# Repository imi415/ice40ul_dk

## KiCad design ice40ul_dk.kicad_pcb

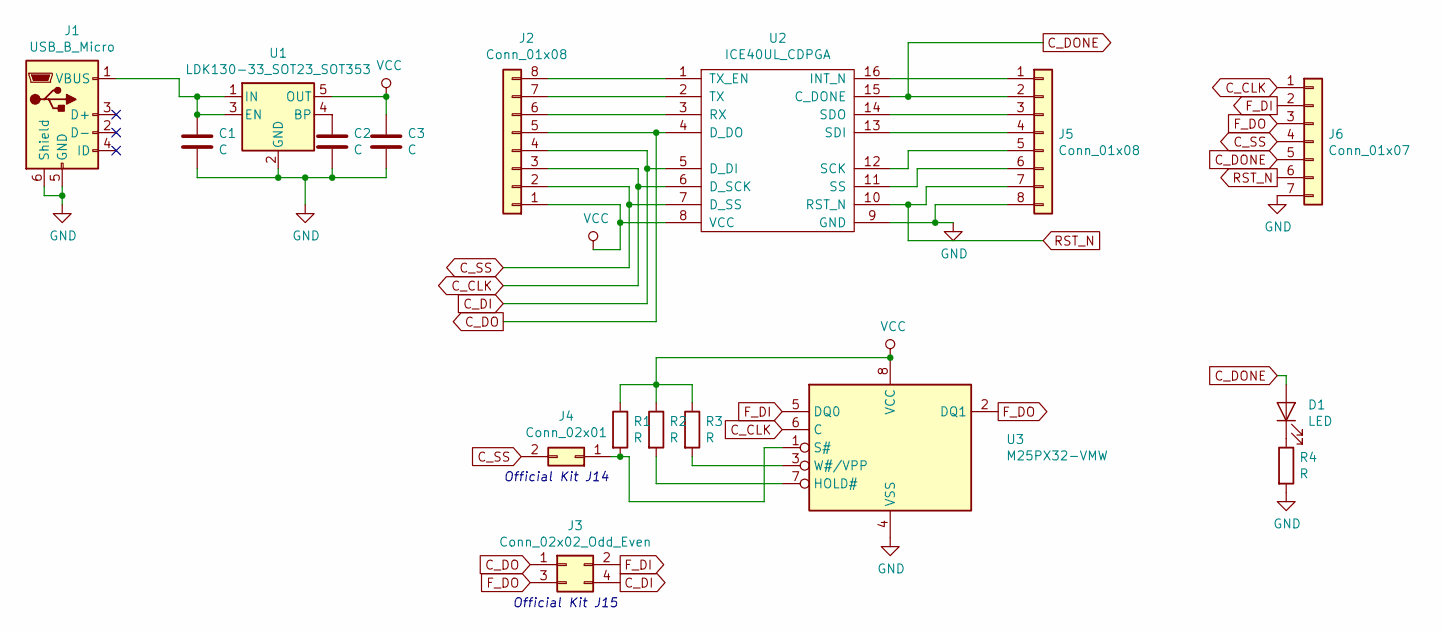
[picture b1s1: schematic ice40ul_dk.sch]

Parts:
C1, C2, C3: C; C_0603_HandSoldering
D1: LED; LED_0603_HandSoldering
J1: USB_B_Micro; USB_Micro-B_Wuerth-629105150521
J2, J5: Conn_01x08; Pin_Header_Straight_1x08_Pitch2.54mm
J3: Conn_02x02_Odd_Even; Pin_Header_Straight_2x02_Pitch2.54mm
J4: Conn_02x01; Pin_Header_Straight_1x02_Pitch2.54mm
J6: Conn_01x07; Pin_Header_Angled_1x07_Pitch2.54mm
R1, R2, R3, R4: R; R_0603_HandSoldering
U1: LDK130-33_SOT23_SOT353; SOT-353_SC-70-5_Handsoldering
U2: ICE40UL_CDPGA; CDPGA_B
U3: M25PX32-VMW; SOIJ-8_5.3x5.3mm_Pitch1.27mm

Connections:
C_CLK: J2.3, J6.1, U2.6 (D_SCK), U3.6 (C)
C_DI: J2.4, J3.4, U2.5 (D_DI)
C_DO: J2.5, J3.1, U2.4 (D_DO)
C_DONE: D1.2 (A), J5.2, J6.5, U2.15 (C_DONE)
C_SS: J2.2, J4.2, J6.4, U2.7 (D_SS)
F_DI: J3.2, J6.2, U3.5 (DQ0)
F_DO: J3.3, J6.3, U3.2 (DQ1)
GND: C1.2, C2.2, C3.2, J1.5 (GND), J1.6 (Shield), J5.8, J6.7, R4.2, U1.2 (GND), U2.9 (GND), U3.4 (VSS)
unnamed: C1.1, J1.1 (VBUS), U1.1 (IN), U1.3 (EN)
unnamed: C2.1, U1.4 (BP)
unnamed: D1.1 (K), R4.1
unnamed: J2.6, U2.3 (RX)
unnamed: J2.7, U2.2 (TX)
unnamed: J2.8, U2.1 (TX_EN)
unnamed: J4.1, R1.2, U3.1 (S#)
unnamed: J5.1, U2.16 (INT_N)
unnamed: J5.3, U2.14 (SDO)
unnamed: J5.4, U2.13 (SDI)
unnamed: J5.5, U2.12 (SCK)
unnamed: J5.6, U2.11 (SS)
unnamed: R2.2, U3.7 (HOLD#)
unnamed: R3.2, U3.3 (W#/VPP)
RST_N: J5.7, J6.6, U2.10 (RST_N)
VCC: C3.1, J2.1, R1.1, R2.1, R3.1, U1.5 (OUT), U2.8 (VCC), U3.8 (VCC)

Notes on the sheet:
Official Kit J14
Official Kit J15

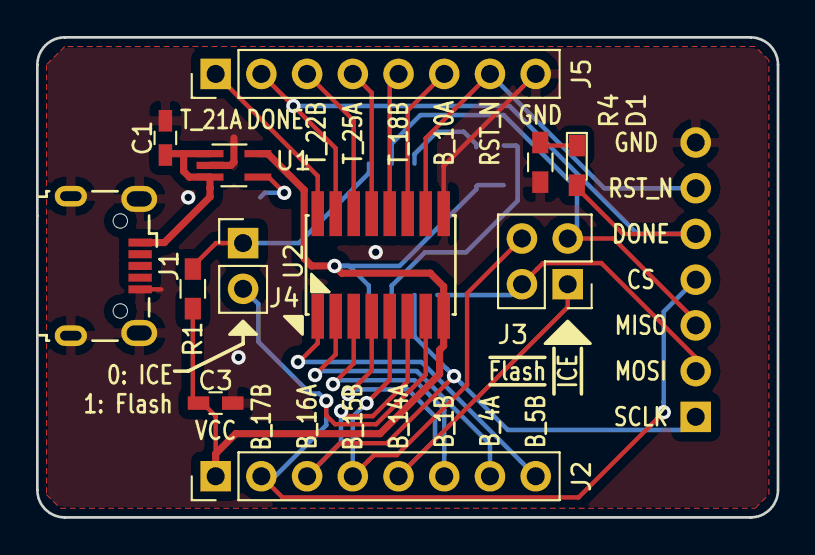
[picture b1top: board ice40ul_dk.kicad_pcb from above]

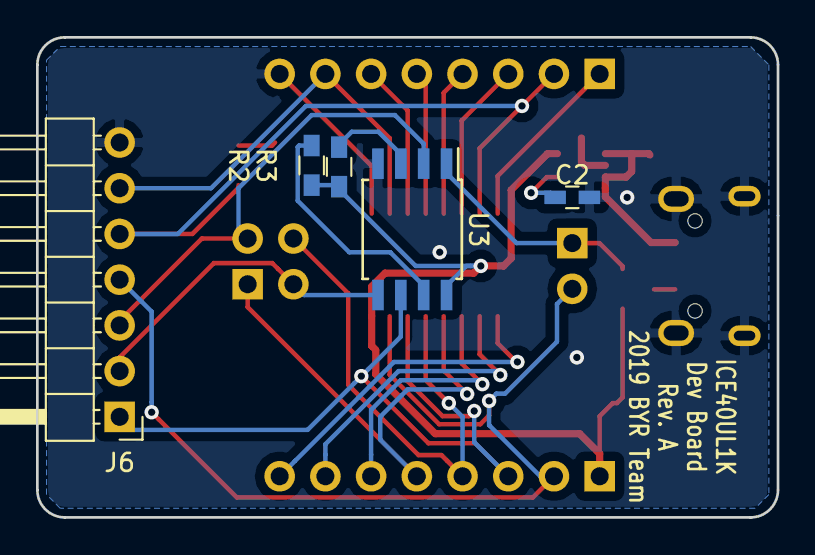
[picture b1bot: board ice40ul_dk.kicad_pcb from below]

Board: 2 copper layers, 41.1 x 26.7 mm, 17 parts (5 on the bottom side), 24 nets.

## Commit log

2019-02-16 Initial commit.
